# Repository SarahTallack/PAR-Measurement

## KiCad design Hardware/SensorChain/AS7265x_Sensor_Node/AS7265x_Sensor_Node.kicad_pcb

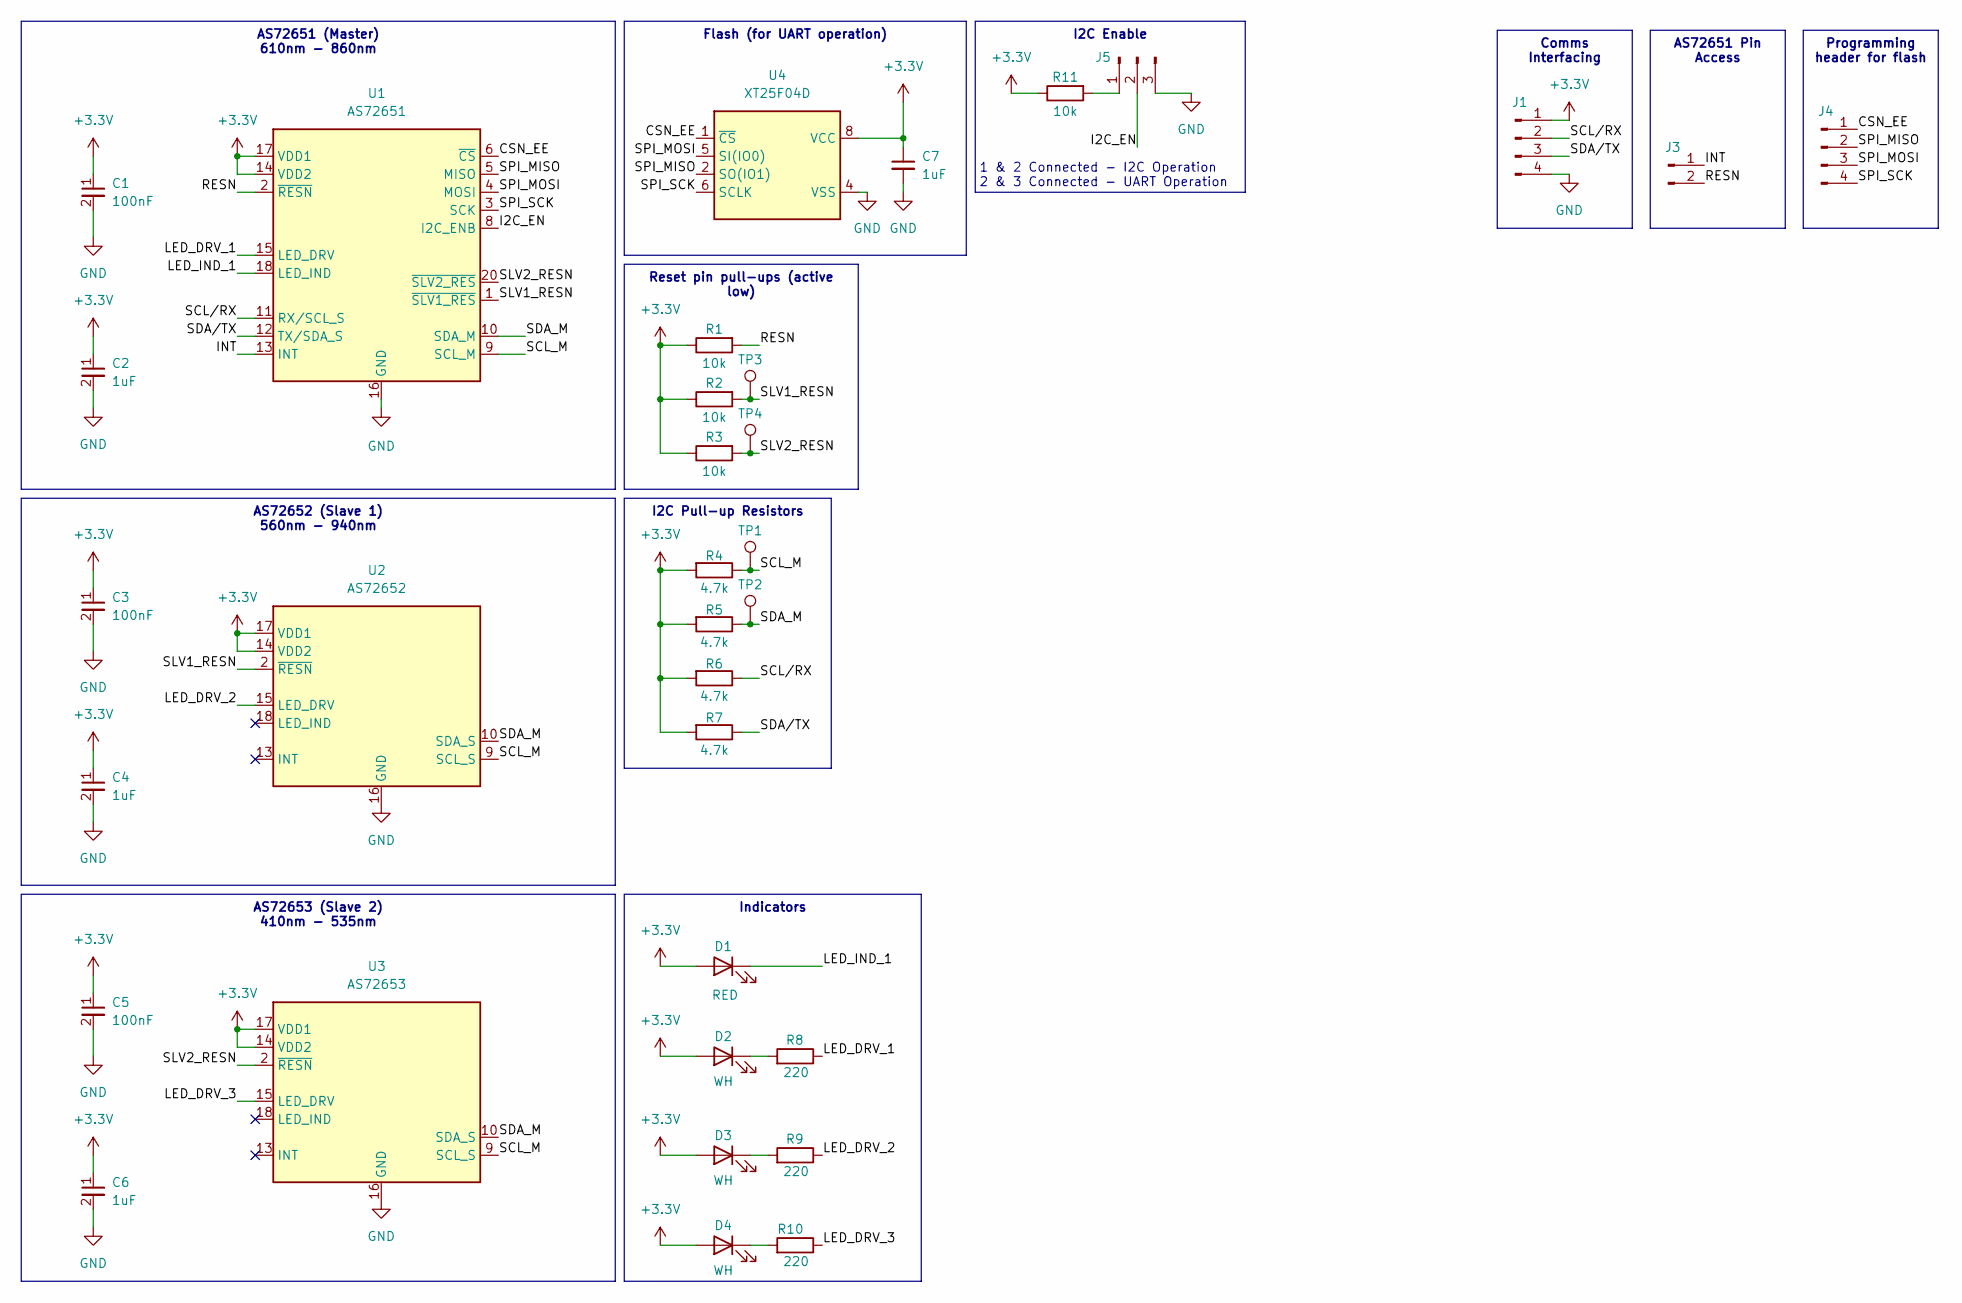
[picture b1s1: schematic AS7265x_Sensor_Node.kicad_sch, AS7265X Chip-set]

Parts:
C1, C3, C5: 100nF; C_0402_1005Metric; LCSC C307331
C2, C4, C6: 1uF; C_0402_1005Metric; LCSC C52923
C7: 1uF; C_0402_1005Metric; LCSC C15849
D1: RED; D_0603_1608Metric; LCSC C2286
D2, D3, D4: WH; D_0603_1608Metric; LCSC C2290
J1, J4: Conn_01x04_Pin; PinHeader_1x04_P2.54mm_Vertical
J3: Conn_01x02_Pin; PinHeader_1x02_P2.54mm_Vertical
J5: Conn_01x03_Pin; PinHeader_1x03_P2.54mm_Vertical
R1, R2, R3, R11: 10k; R_0402_1005Metric; LCSC C25744
R4, R5, R6, R7: 4.7k; R_0402_1005Metric; LCSC C25744
R8, R9, R10: 220; R_0402_1005Metric; LCSC C25091
TP1, TP2, TP3, TP4: TestPoint; TestPoint_Plated_Hole_D2.0mm
U1: AS72651; AMS_AS7265x_LGA-20_4.7x4.5mm_P0.65mm
U2: AS72652; AMS_AS7265x_LGA-20_4.7x4.5mm_P0.65mm
U3: AS72653; AMS_AS7265x_LGA-20_4.7x4.5mm_P0.65mm
U4: XT25F04D; SOP-8_3.9x4.9mm_P1.27mm; LCSC C558854

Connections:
+3.3V: C1.1, C2.1, C3.1, C4.1, C5.1, C6.1, C7.1, D1.2 (A), D2.2 (A), D3.2 (A), D4.2 (A), J1.1, R1.1, R2.1, R3.1, R4.2, R5.2, R6.2, R7.2, R11.1, U1.14 (VDD2), U1.17 (VDD1), U2.14 (VDD2), U2.17 (VDD1), U3.14 (VDD2), U3.17 (VDD1), U4.8 (VCC)
/CSN_EE: J4.1, U1.6 (~CS), U4.1 (~CS)
/I2C_EN: J5.2, U1.8 (I2C_ENB)
/INT: J3.1, U1.13 (INT)
/LED_DRV_1: R8.1, U1.15 (LED_DRV)
/LED_DRV_2: R9.1, U2.15 (LED_DRV)
/LED_DRV_3: R10.1, U3.15 (LED_DRV)
/LED_IND_1: D1.1 (K), U1.18 (LED_IND)
/RESN: J3.2, R1.2, U1.2 (~RESN)
/SCL_M: R4.1, TP1.1, U1.9 (SCL_M), U2.9 (SCL_S), U3.9 (SCL_S)
/SCL/RX: J1.2, R6.1, U1.11 (RX/SCL_S)
/SDA_M: R5.1, TP2.1, U1.10 (SDA_M), U2.10 (SDA_S), U3.10 (SDA_S)
/SDA/TX: J1.3, R7.1, U1.12 (TX/SDA_S)
/SLV1_RESN: R2.2, TP3.1, U1.1 (~SLV1_RES), U2.2 (~RESN)
/SLV2_RESN: R3.2, TP4.1, U1.20 (~SLV2_RES), U3.2 (~RESN)
/SPI_MISO: J4.2, U1.5 (MISO), U4.2 (SO(IO1))
/SPI_MOSI: J4.3, U1.4 (MOSI), U4.5 (SI(IO0))
/SPI_SCK: J4.4, U1.3 (SCK), U4.6 (SCLK)
GND: C1.2, C2.2, C3.2, C4.2, C5.2, C6.2, C7.2, J1.4, J5.3, U1.16 (GND), U2.16 (GND), U3.16 (GND), U4.4 (VSS)
unnamed: D2.1 (K), R8.2
unnamed: D3.1 (K), R9.2
unnamed: D4.1 (K), R10.2
unnamed: J5.1, R11.2

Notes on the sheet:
AS72651 (Master) 610nm - 860nm
AS72651 Pin Access
Reset pin pull-ups (active low)
Programming header for flash
AS72653 (Slave 2) 410nm - 535nm
Comms Interfacing
Indicators
I2C Enable
AS72652 (Slave 1) 560nm - 940nm
I2C Pull-up Resistors
Flash (for UART operation)
1 & 2 Connected - I2C Operation 2 & 3 Connected - UART Operation

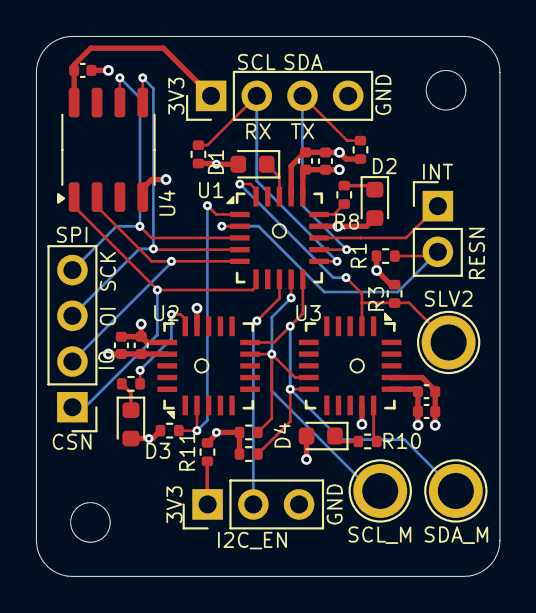
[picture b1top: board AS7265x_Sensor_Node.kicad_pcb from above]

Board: 4 copper layers, 25.8 x 30.0 mm, 33 parts (0 on the bottom side), 23 nets.

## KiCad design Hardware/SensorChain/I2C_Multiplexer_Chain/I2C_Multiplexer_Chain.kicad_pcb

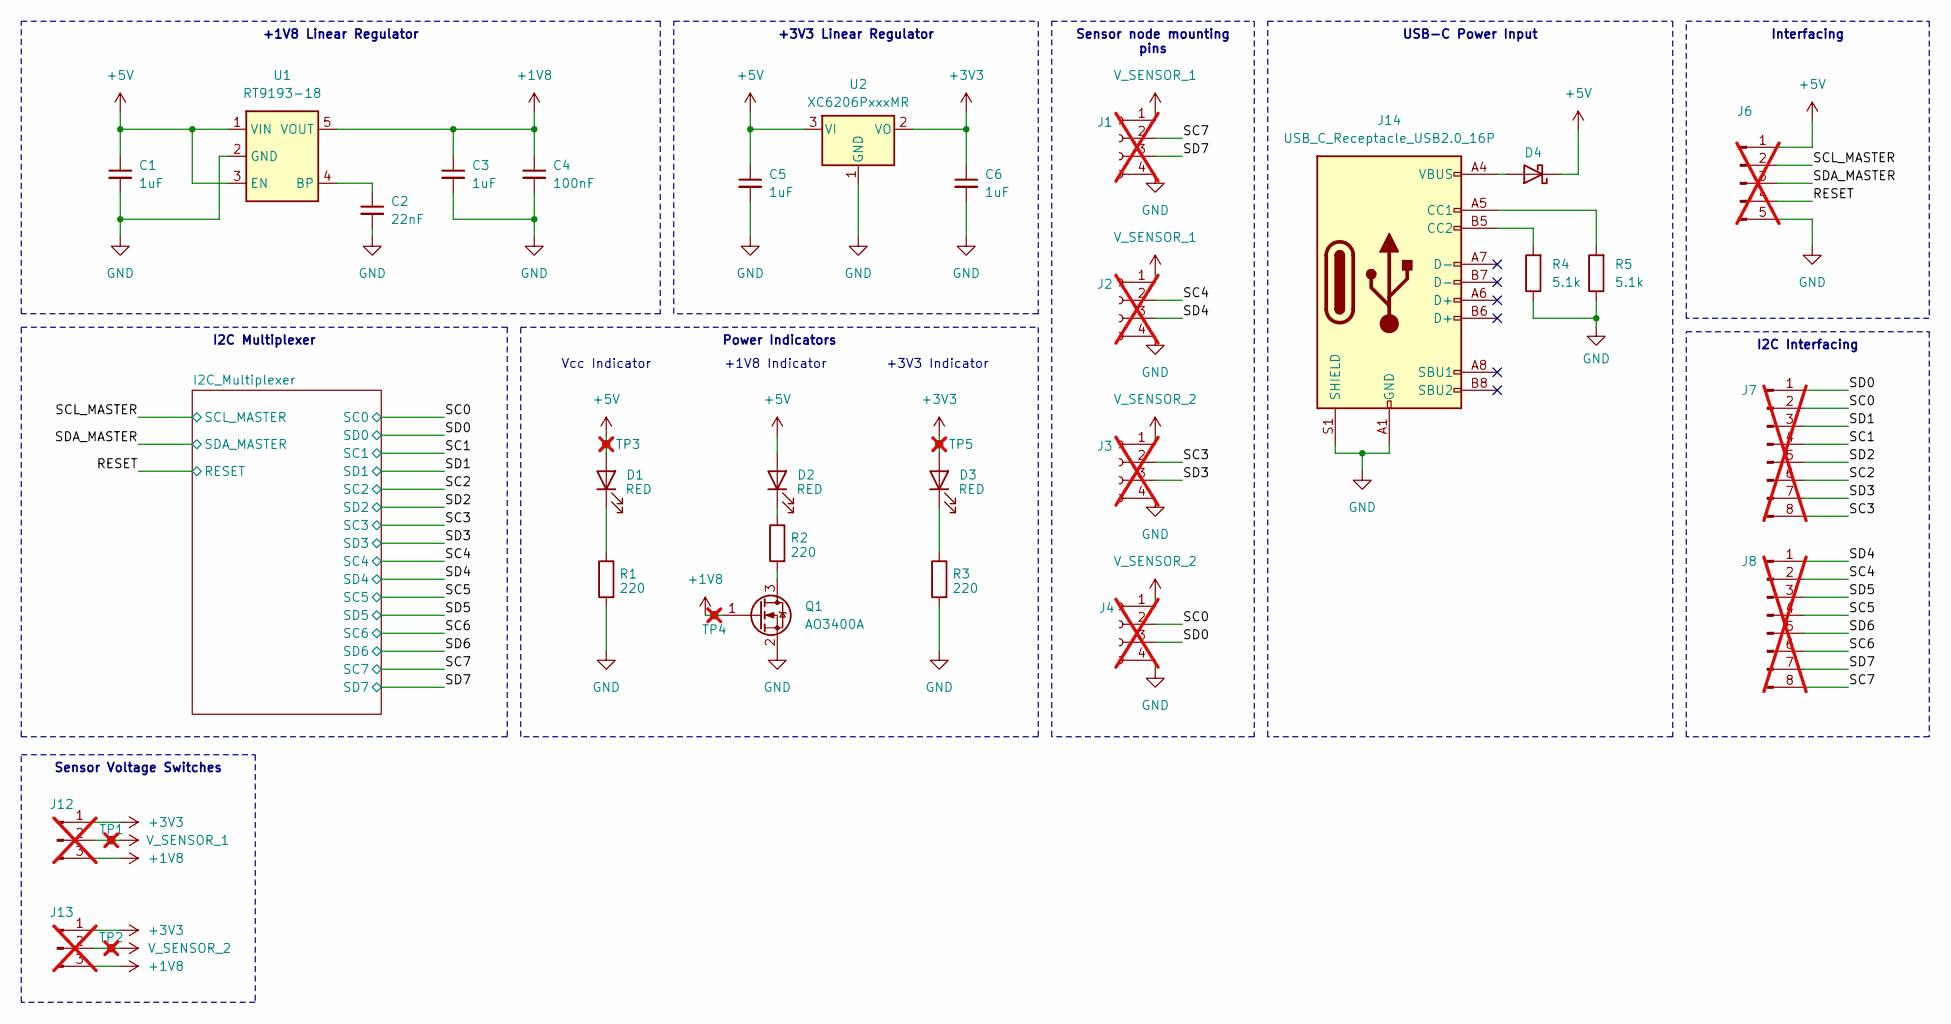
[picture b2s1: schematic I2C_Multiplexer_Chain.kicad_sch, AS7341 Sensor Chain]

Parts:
C1, C3, C5, C6: 1uF; C_0603_1608Metric; LCSC C15849
C2: 22nF; C_0603_1608Metric; LCSC C21122
C4: 100nF; C_0603_1608Metric; LCSC C14663
D1, D2, D3: RED; D_0603_1608Metric; LCSC C2286
D4: D_Schottky; D_SMA; LCSC C2480
J1, J2, J3, J4: Conn_01x04_Socket; PinSocket_1x04_P2.54mm_Vertical; not fitted
J6: Conn_01x05_Pin; PinHeader_1x05_P2.54mm_Vertical; not fitted
J7, J8: Conn_01x08_Pin; PinHeader_1x08_P2.54mm_Vertical; not fitted
J12, J13: Conn_01x03_Pin; PinHeader_1x03_P2.54mm_Vertical; not fitted
J14: USB_C_Receptacle_USB2.0_16P; USB_C_Receptacle_GCT_USB4105-xx-A_16P_TopMnt_Horizontal; LCSC C2927038
Q1: AO3400A; SOT-23; LCSC C20917
R1, R2, R3: 220; R_0603_1608Metric; LCSC C22962
R4, R5: 5.1k; R_0805_2012Metric; LCSC C27834
TP1, TP2, TP3, TP4, TP5: TestPoint_Small; TestPoint_THTPad_D2.0mm_Drill1.0mm; not fitted
U1: RT9193-18; SOT-23-5; LCSC C27416
U2: XC6206PxxxMR; SOT-23-3; LCSC C5446

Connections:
+1V8: C3.1, C4.1, J12.3, J13.3, Q1.1 (G), TP4.1, U1.5 (VOUT)
+3V3: C6.1, D3.2 (A), J12.1, J13.1, TP5.1, U2.2 (VO); also elsewhere on the board
+5V: C1.1, C5.1, D1.2 (A), D2.2 (A), D4.1 (K), J6.1, TP3.1, U1.1 (VIN), U1.3 (EN), U2.3 (VI)
/RESET: J6.4; also elsewhere on the board
/SC0: J4.2, J7.2; also elsewhere on the board
/SC1: J7.4; also elsewhere on the board
/SC2: J7.6; also elsewhere on the board
/SC3: J3.2, J7.8; also elsewhere on the board
/SC4: J2.2, J8.2; also elsewhere on the board
/SC5: J8.4; also elsewhere on the board
/SC6: J8.6; also elsewhere on the board
/SC7: J1.2, J8.8; also elsewhere on the board
/SCL_MASTER: J6.2; also elsewhere on the board
/SD0: J4.3, J7.1; also elsewhere on the board
/SD1: J7.3; also elsewhere on the board
/SD2: J7.5; also elsewhere on the board
/SD3: J3.3, J7.7; also elsewhere on the board
/SD4: J2.3, J8.1; also elsewhere on the board
/SD5: J8.3; also elsewhere on the board
/SD6: J8.5; also elsewhere on the board
/SD7: J1.3, J8.7; also elsewhere on the board
/SDA_MASTER: J6.3; also elsewhere on the board
GND: C1.2, C2.2, C3.2, C4.2, C5.2, C6.2, J1.4, J2.4, J3.4, J4.4, J6.5, J14.A1 (GND), J14.A12 (GND), J14.B1 (GND), J14.B12 (GND), J14.S1 (SHIELD), Q1.2 (S), R1.2, R3.2, R4.1, R5.1, U1.2 (GND), U2.1 (GND); also elsewhere on the board
unnamed: D1.1 (K), R1.1
unnamed: D2.1 (K), R2.1
unnamed: D3.1 (K), R3.1
unnamed: D4.2 (A), J14.A4 (VBUS), J14.A9 (VBUS), J14.B4 (VBUS), J14.B9 (VBUS)
unnamed: J14.A5 (CC1), R5.2
unnamed: J14.B5 (CC2), R4.2
unnamed: Q1.3 (D), R2.2
unnamed: C2.1, U1.4 (BP)
V_SENSOR_1: J1.1, J2.1, J12.2, TP1.1
V_SENSOR_2: J3.1, J4.1, J13.2, TP2.1

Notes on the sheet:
USB-C Power Input
Sensor Voltage Switches
Sensor node mounting pins
+3V3 Linear Regulator
Power Indicators
I2C Interfacing
I2C Multiplexer
+1V8 Linear Regulator
Interfacing
+3V3 Indicator
+1V8 Indicator
Vcc Indicator

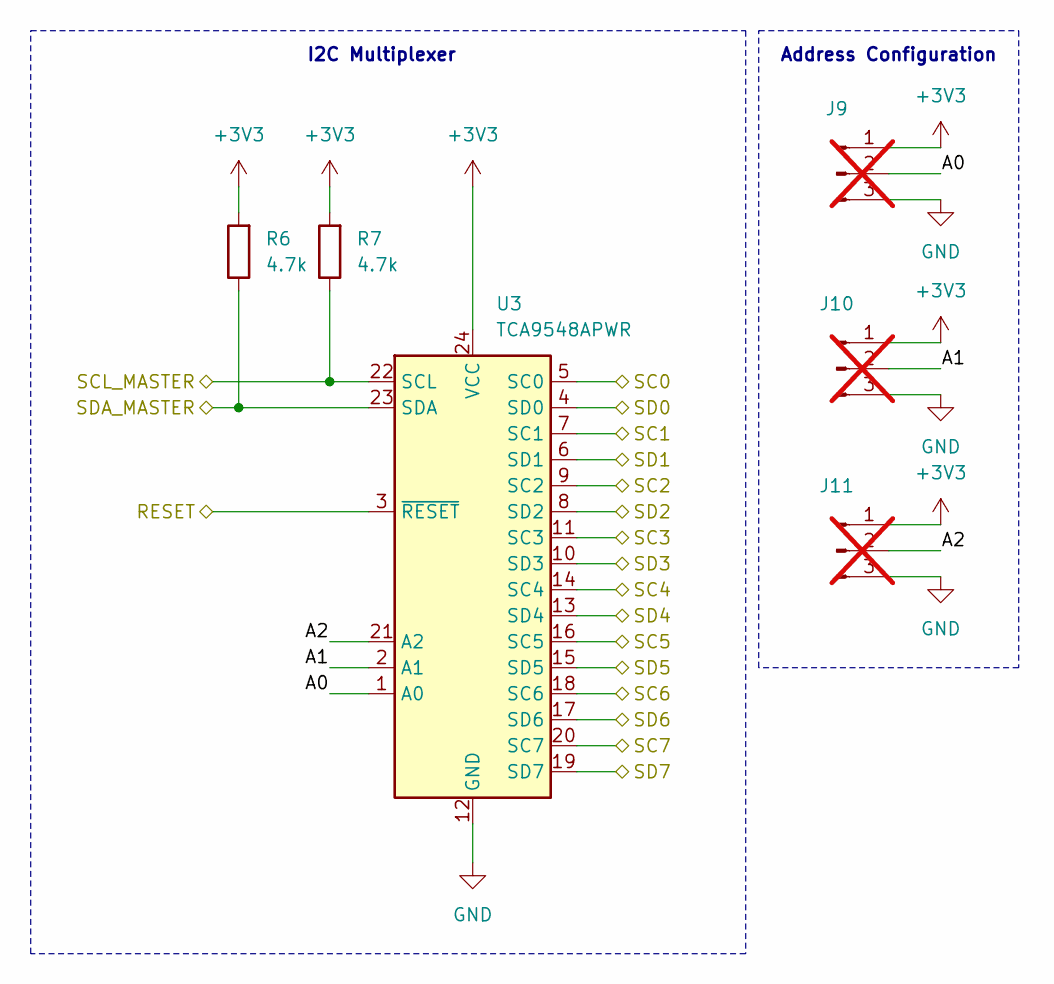
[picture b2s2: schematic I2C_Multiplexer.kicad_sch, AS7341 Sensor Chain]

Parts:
J9, J10, J11: Conn_01x03_Pin; PinHeader_1x03_P2.54mm_Vertical; not fitted
R6, R7: 4.7k; R_0603_1608Metric; LCSC C23162
U3: TCA9548APWR; TSSOP-24_4.4x7.8mm_P0.65mm; LCSC C130026

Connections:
+3V3: J9.1, J10.1, J11.1, R6.2, R7.2, U3.24 (VCC); also elsewhere on the board
/I2C_Multiplexer/A0: J9.2, U3.1 (A0)
/I2C_Multiplexer/A1: J10.2, U3.2 (A1)
/I2C_Multiplexer/A2: J11.2, U3.21 (A2)
/RESET: U3.3 (~RESET); also elsewhere on the board
/SC0: U3.5 (SC0); also elsewhere on the board
/SC1: U3.7 (SC1); also elsewhere on the board
/SC2: U3.9 (SC2); also elsewhere on the board
/SC3: U3.11 (SC3); also elsewhere on the board
/SC4: U3.14 (SC4); also elsewhere on the board
/SC5: U3.16 (SC5); also elsewhere on the board
/SC6: U3.18 (SC6); also elsewhere on the board
/SC7: U3.20 (SC7); also elsewhere on the board
/SCL_MASTER: R7.1, U3.22 (SCL); also elsewhere on the board
/SD0: U3.4 (SD0); also elsewhere on the board
/SD1: U3.6 (SD1); also elsewhere on the board
/SD2: U3.8 (SD2); also elsewhere on the board
/SD3: U3.10 (SD3); also elsewhere on the board
/SD4: U3.13 (SD4); also elsewhere on the board
/SD5: U3.15 (SD5); also elsewhere on the board
/SD6: U3.17 (SD6); also elsewhere on the board
/SD7: U3.19 (SD7); also elsewhere on the board
/SDA_MASTER: R6.1, U3.23 (SDA); also elsewhere on the board
GND: J9.3, J10.3, J11.3, U3.12 (GND); also elsewhere on the board

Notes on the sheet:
I2C Multiplexer
Address Configuration

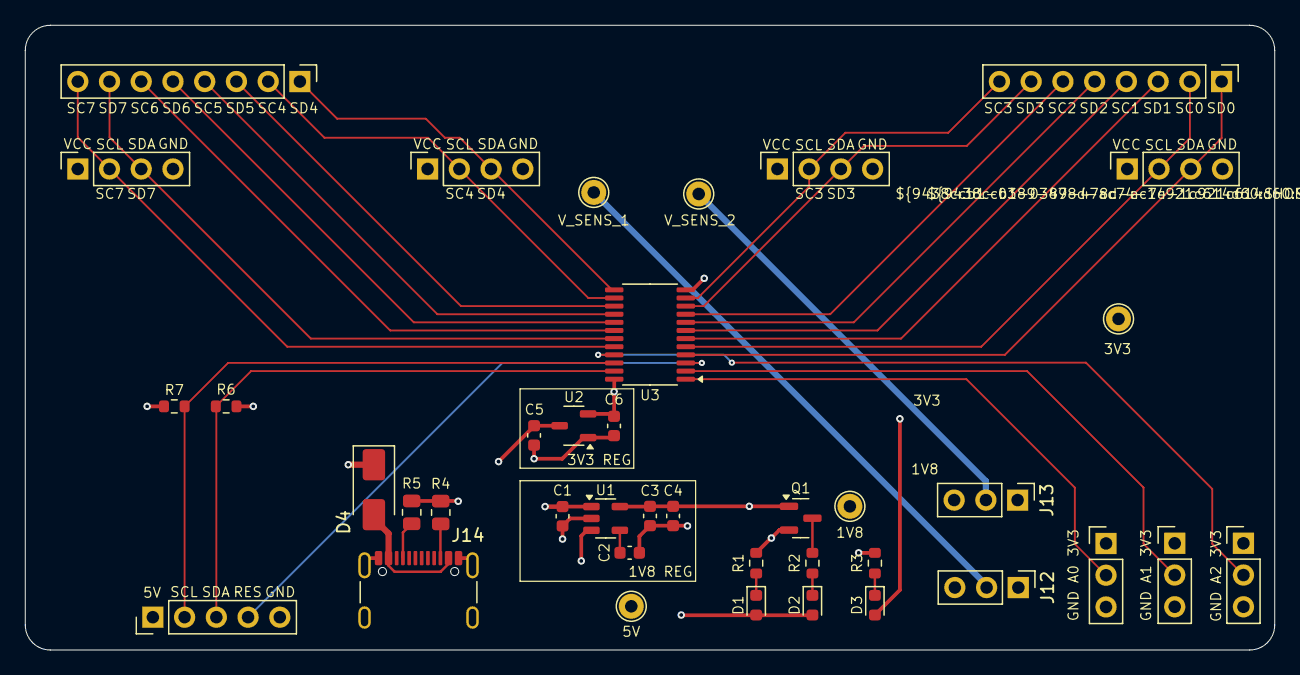
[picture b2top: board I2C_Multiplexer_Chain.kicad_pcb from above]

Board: 4 copper layers, 100.0 x 50.0 mm, 39 parts (0 on the bottom side), 36 nets.

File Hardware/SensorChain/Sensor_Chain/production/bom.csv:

Designator,Footprint,Quantity,Value,LCSC Part #
"C1, C3, C5, C6",0603,4,1uF,C15849
C2,0603,1,22nF,C21122
C4,0603,1,100nF,C14663
"D1, D2, D3",0603,3,RED,C2286
D4,D_SMA,1,D_Schottky,C2480
J14,USB_C_Receptacle_GCT_USB4105-xx-A_16P_TopMnt_Horizontal,1,USB_C_Receptacle_USB2.0_16P,C2927038
Q1,SOT-23,1,AO3400A,C20917
"R1, R2, R3",0603,3,220,C22962
"R4, R5",0805,2,5.1k,C27834
"R6, R7",0603,2,4.7k,C23162
U1,SOT-23-5,1,RT9193-18,C27416
U2,SOT-23-3,1,XC6206PxxxMR,C5446
U3,TSSOP-24_4.4x7.8mm_P0.65mm,1,TCA9548APWR,C130026

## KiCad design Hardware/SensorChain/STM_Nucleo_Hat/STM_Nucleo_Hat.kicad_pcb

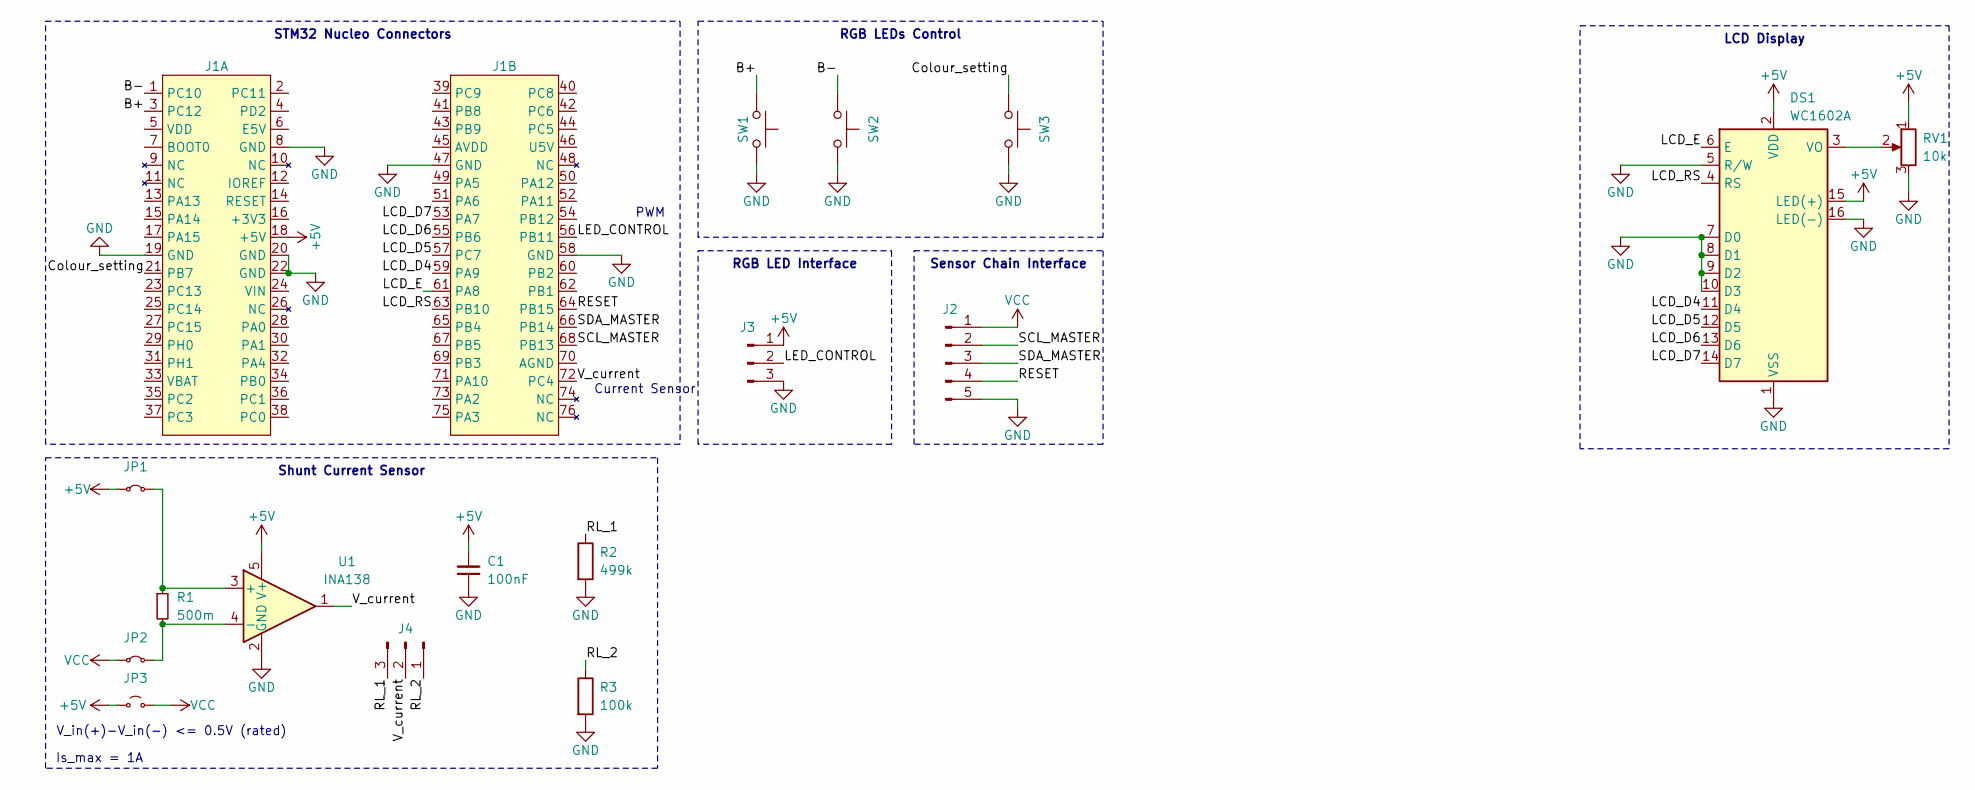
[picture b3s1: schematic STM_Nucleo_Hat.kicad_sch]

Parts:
C1: 100nF; C_0603_1608Metric; LCSC C307331
DS1: WC1602A
J1: Nucleo64-Pins
J2: Conn_01x05_Pin; PinHeader_1x05_P2.54mm_Vertical
J3, J4: Conn_01x03_Pin; PinHeader_1x03_P2.54mm_Vertical
JP1, JP2: Jumper_2_Small_Closed; SolderJumper-2_P1.3mm_Bridged_RoundedPad1.0x1.5mm
JP3: Jumper_2_Small_Open; SolderJumper-2_P1.3mm_Open_RoundedPad1.0x1.5mm
R1: 500m; R_1206_3216Metric; LCSC C601092
R2: 499k; R_0402_1005Metric; LCSC C137971
R3: 100k; R_0402_1005Metric; LCSC C25741
RV1: 10k; Potentiometer_Bourns_TC33X_Vertical; LCSC C719176
SW1, SW2, SW3: SW_Push; SW_Push_1P1T_XKB_TS-1187A; LCSC C318884
U1: INA138; SOT-23-5; LCSC C47914

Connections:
+5V: C1.2, DS1.2 (VDD), DS1.15 (LED(+)), J1.18 (+5V), J3.1, JP1.1 (A), JP3.1 (A), RV1.1, U1.5 (V+)
/B+: J1.3 (PC12), SW1.1
/B-: J1.1 (PC10), SW2.1
/Colour_setting: J1.21 (PB7), SW3.1
/LCD_D4: DS1.11 (D4), J1.59 (PA9)
/LCD_D5: DS1.12 (D5), J1.57 (PC7)
/LCD_D6: DS1.13 (D6), J1.55 (PB6)
/LCD_D7: DS1.14 (D7), J1.53 (PA7)
/LCD_E: DS1.6 (E), J1.61 (PA8)
/LCD_RS: DS1.4 (RS), J1.63 (PB10)
/LED_CONTROL: J1.56 (PB11), J3.2
/RESET: J1.64 (PB15), J2.4
/RL_1: J4.3, R2.1
/RL_2: J4.1, R3.1
/SCL_MASTER: J1.68 (PB13), J2.2
/SDA_MASTER: J1.66 (PB14), J2.3
/V_current: J1.72 (PC4), J4.2, U1.1
GND: C1.1, DS1.1 (VSS), DS1.5 (R/W), DS1.7 (D0), DS1.8 (D1), DS1.9 (D2), DS1.10 (D3), DS1.16 (LED(-)), J1.8 (GND), J1.19 (GND), J1.20 (GND), J1.22 (GND), J1.47 (GND), J1.58 (GND), J2.5, J3.3, R2.2, R3.2, RV1.3, SW1.2, SW2.2, SW3.2, U1.2 (GND)
unnamed: DS1.3 (VO), RV1.2
unnamed: JP1.2 (B), R1.1, U1.3 (+)
unnamed: JP2.2 (B), R1.2, U1.4 (-)
VCC: J2.1, JP2.1 (A), JP3.2 (B)

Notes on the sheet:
Sensor Chain Interface
Shunt Current Sensor
STM32 Nucleo Connectors
RGB LED Interface
RGB LEDs Control
LCD Display
Is_max = 1A
V_in(+)-V_in(-) <= 0.5V (rated)
PWM
Current Sensor

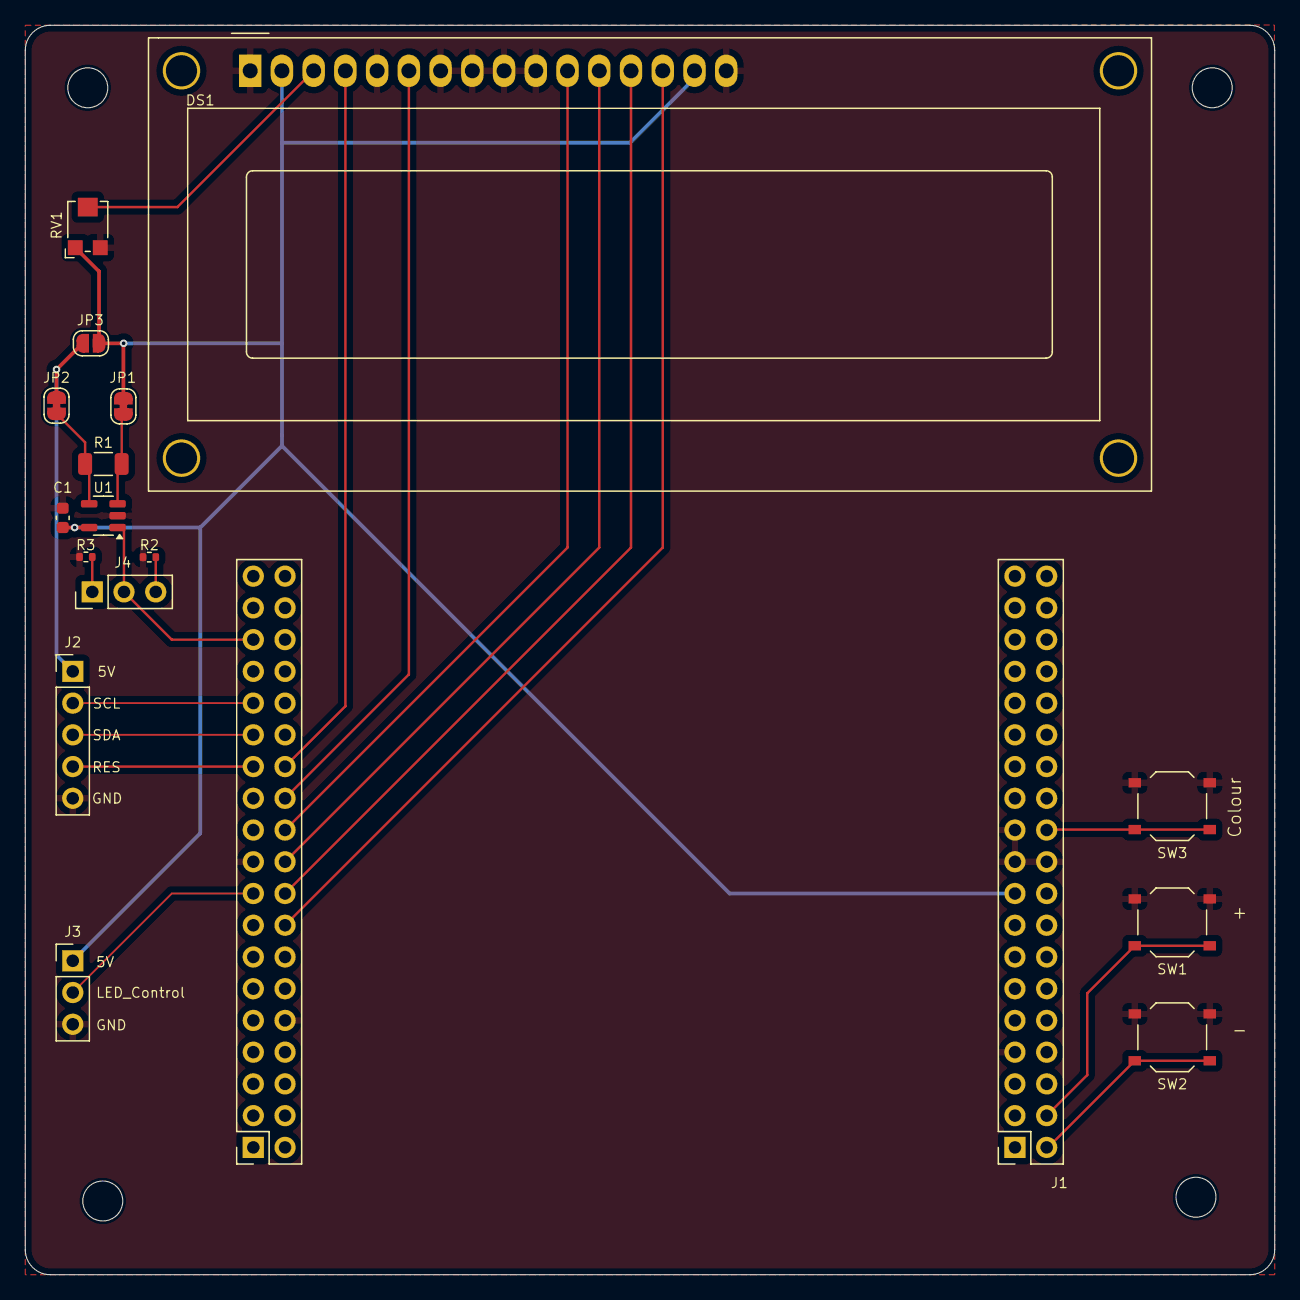
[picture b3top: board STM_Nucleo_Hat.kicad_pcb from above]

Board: 2 copper layers, 100.0 x 100.0 mm, 17 parts (0 on the bottom side), 22 nets.

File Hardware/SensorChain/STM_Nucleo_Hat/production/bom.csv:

Designator,Footprint,Quantity,Value,LCSC Part #
C1,0603,1,100nF,C307331
R1,1206,1,500m,C601092
R2,0402,1,499k,C137971
R3,0402,1,100k,C25741
RV1,Potentiometer_Bourns_TC33X_Vertical,1,10k,C719176
"SW1, SW2, SW3",SW_Push_1P1T_XKB_TS-1187A,3,SW_Push,C318884
U1,SOT-23-5,1,INA138,C47914

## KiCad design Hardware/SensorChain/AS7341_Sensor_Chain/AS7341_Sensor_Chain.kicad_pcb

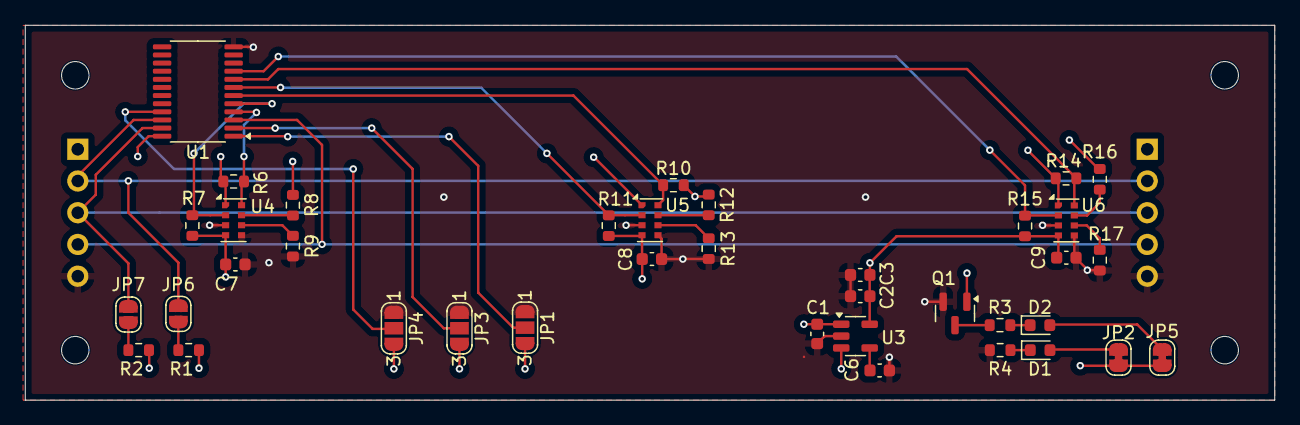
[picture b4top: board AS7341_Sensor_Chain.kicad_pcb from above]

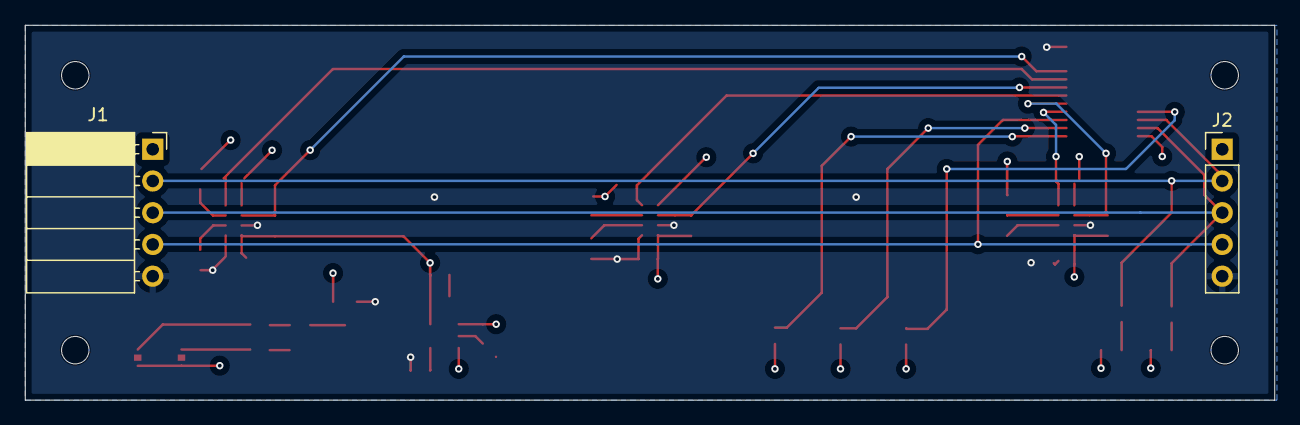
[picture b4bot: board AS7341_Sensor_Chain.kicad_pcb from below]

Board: 4 copper layers, 100.0 x 30.0 mm, 40 parts (2 on the bottom side), 29 nets.

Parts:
C1, C2: 1uF; C_0603_1608Metric
C3, C7, C8, C9: 100nF; C_0603_1608Metric
C6: 22nF; C_0603_1608Metric
D1, D2: RED; D_0603_1608Metric
J1: Conn_01x05_Pin; PinSocket_1x05_P2.54mm_Horizontal
J2: Conn_01x05_Pin; PinHeader_1x05_P2.54mm_Vertical
JP1, JP3, JP4: SolderJumper_3_Open; SolderJumper-3_P1.3mm_Open_RoundedPad1.0x1.5mm_NumberLabels
JP2, JP5: SolderJumper_2_Bridged; SolderJumper-2_P1.3mm_Bridged_RoundedPad1.0x1.5mm
JP6, JP7: SolderJumper_2_Open; SolderJumper-2_P1.3mm_Open_RoundedPad1.0x1.5mm
Q1: AO3400A; SOT-23
R1, R2, R3, R4, R6, R7, R10, R11, R14, R15: 4.7k; R_0603_1608Metric
R8, R9, R12, R13, R16, R17: 10k; R_0603_1608Metric
U1: TCA9548APWR; TSSOP-24_4.4x7.8mm_P0.65mm
U3: RT9193-18; SOT-23-5
U4, U5, U6: AS7341DLG; AMS_OLGA-8_2x3.1mm_P0.8mm

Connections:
+1V8: C2.1, C3.1, C7.2, C8.2, C9.2, Q1.1 (G), R6.2, R7.2, R8.2, R10.2, R11.2, R12.2, R14.2, R15.2, R16.2, U3.5 (VOUT), U4.1 (VDD), U4.4 (LDR), U5.1 (VDD), U5.4 (LDR), U6.1 (VDD), U6.4 (LDR)
/A0: JP1.2 (C), U1.1 (A0)
/A1: JP3.2 (C), U1.2 (A1)
/A2: JP4.2 (C), U1.21 (A2)
/AS7341_0/GPIO: R9.2, U4.6 (GPIO)
/AS7341_0/INT: R8.1, U4.7 (INT)
/AS7341_1/GPIO: R13.2, U5.6 (GPIO)
/AS7341_1/INT: R12.1, U5.7 (INT)
/AS7341_2/GPIO: R17.2, U6.6 (GPIO)
/AS7341_2/INT: R16.1, U6.7 (INT)
/RESET: J1.4, J2.4, U1.3 (~RESET)
/SC0: R7.1, U1.5 (SC0), U4.2 (SCL)
/SC1: R11.1, U1.7 (SC1), U5.2 (SCL)
/SC2: R15.1, U1.9 (SC2), U6.2 (SCL)
/SCL_MASTER: J1.2, J2.2, JP6.1 (A), U1.22 (SCL)
/SD0: R6.1, U1.4 (SD0), U4.8 (SDA)
/SD1: R10.1, U1.6 (SD1), U5.8 (SDA)
/SD2: R14.1, U1.8 (SD2), U6.8 (SDA)
/SDA_MASTER: J1.3, J2.3, JP7.1 (A), U1.23 (SDA)
GND: C1.2, C2.2, C3.2, C6.2, C7.1, C8.1, C9.1, J1.5, J2.5, JP1.1 (A), JP3.1 (A), JP4.1 (A), Q1.2 (S), R4.1, R9.1, R13.1, R17.1, U1.12 (GND), U3.2 (GND), U4.3 (GND), U4.5 (PGND), U5.3 (GND), U5.5 (PGND), U6.3 (GND), U6.5 (PGND)
unnamed: D1.2 (A), JP2.1 (A)
unnamed: D1.1 (K), R4.2
unnamed: D2.2 (A), JP5.1 (A)
unnamed: D2.1 (K), R3.2
unnamed: JP6.2 (B), R1.1
unnamed: JP7.2 (B), R2.1
unnamed: Q1.3 (D), R3.1
unnamed: C6.1, U3.4 (BP)
VCC: C1.1, J1.1, J2.1, JP1.3 (B), JP2.2 (B), JP3.3 (B), JP4.3 (B), JP5.2 (B), R1.2, R2.2, U1.24 (VCC), U3.1 (VIN), U3.3 (EN)

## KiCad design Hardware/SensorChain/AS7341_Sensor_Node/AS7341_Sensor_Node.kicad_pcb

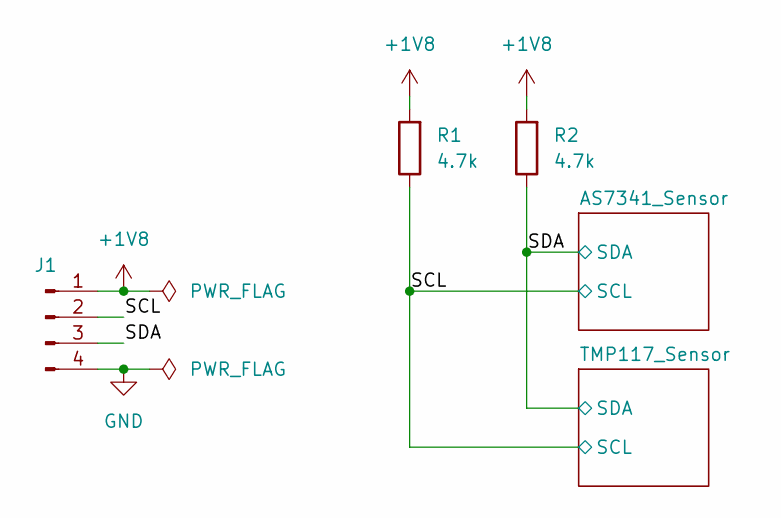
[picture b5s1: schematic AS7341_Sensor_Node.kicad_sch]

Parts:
J1: Conn_01x04_Pin; PinHeader_1x04_P2.54mm_Vertical
R1, R2: 4.7k; R_0603_1608Metric; LCSC C25900

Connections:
+1V8: J1.1, R1.2, R2.2; also elsewhere on the board
/SCL: J1.2, R1.1; also elsewhere on the board
/SDA: J1.3, R2.1; also elsewhere on the board
GND: J1.4; also elsewhere on the board

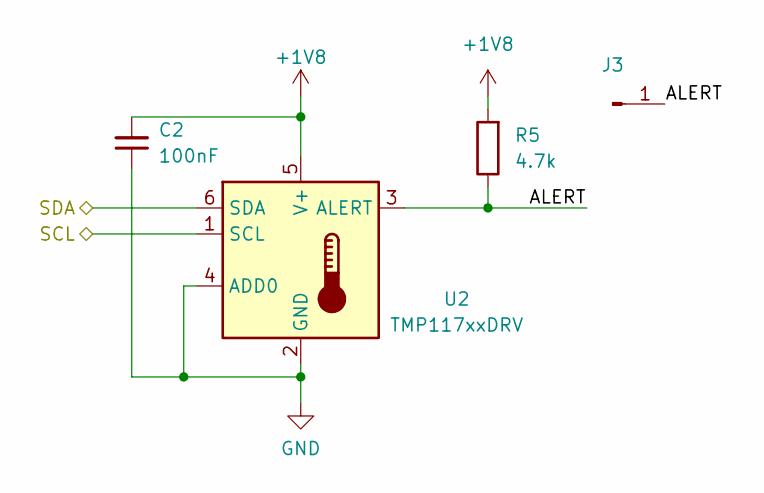
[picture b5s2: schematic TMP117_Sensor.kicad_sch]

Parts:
C2: 100nF; C_0603_1608Metric; LCSC C307331
J3: Conn_01x01_Pin; PinHeader_1x01_P2.54mm_Vertical
R5: 4.7k; R_0603_1608Metric; LCSC C25900
U2: TMP117xxDRV; WSON-6-1EP_2x2mm_P0.65mm_EP1x1.6mm; LCSC C699536

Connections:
+1V8: C2.2, R5.2, U2.5 (V+); also elsewhere on the board
/SCL: U2.1 (SCL); also elsewhere on the board
/SDA: U2.6 (SDA); also elsewhere on the board
/TMP117_Sensor/ALERT: J3.1, R5.1, U2.3 (ALERT)
GND: C2.1, U2.2 (GND), U2.4 (ADD0); also elsewhere on the board

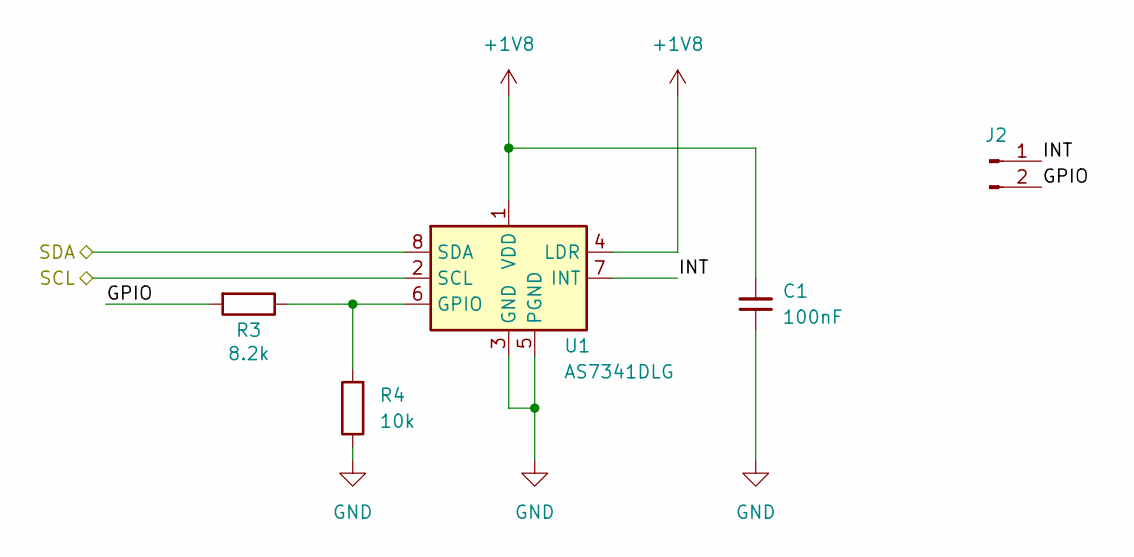
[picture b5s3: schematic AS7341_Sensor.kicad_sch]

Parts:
C1: 100nF; C_0603_1608Metric; LCSC C307331
J2: Conn_01x02_Pin; PinHeader_1x02_P2.54mm_Vertical
R3: 8.2k; R_0603_1608Metric; LCSC C25981
R4: 10k; R_0603_1608Metric; LCSC C25744
U1: AS7341DLG; AMS_OLGA-8_2x3.1mm_P0.8mm; LCSC C2649486

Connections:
+1V8: C1.2, U1.1 (VDD), U1.4 (LDR); also elsewhere on the board
/AS7341_Sensor/GPIO: J2.2, R3.2
/AS7341_Sensor/INT: J2.1, U1.7 (INT)
/SCL: U1.2 (SCL); also elsewhere on the board
/SDA: U1.8 (SDA); also elsewhere on the board
GND: C1.1, R4.1, U1.3 (GND), U1.5 (PGND); also elsewhere on the board
unnamed: R3.1, R4.2, U1.6 (GPIO)

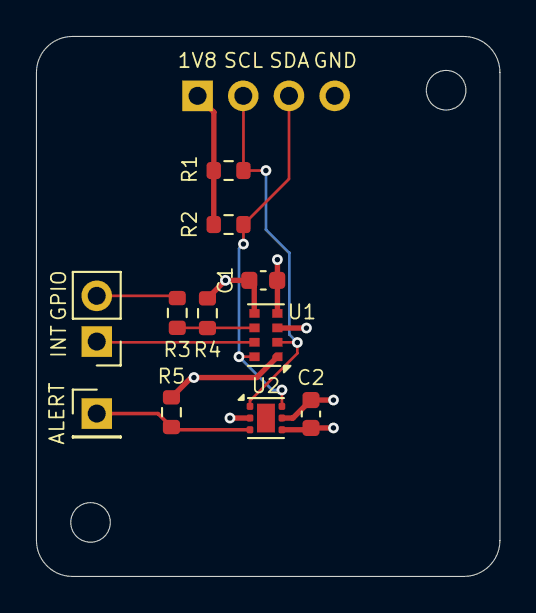
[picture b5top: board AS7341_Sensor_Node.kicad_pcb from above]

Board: 4 copper layers, 25.8 x 30.0 mm, 12 parts (1 on the bottom side), 8 nets.
